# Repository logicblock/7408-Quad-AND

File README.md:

### Logic Block 7408 - Quad 2-input AND gates

*Scale 1:1*

### Where to buy it?
Coming soon on Tindie

### Licence
**Logic Block 7408 - Quad 2-input AND gates** are licenced under [Creative Commons Attribution and Share Alike 4.0 International](https://github.com/logicblock/7408-Quad-AND/blob/master/LICENSE.md) by [J.Rodrigo](http://www.jrodrigo.net).

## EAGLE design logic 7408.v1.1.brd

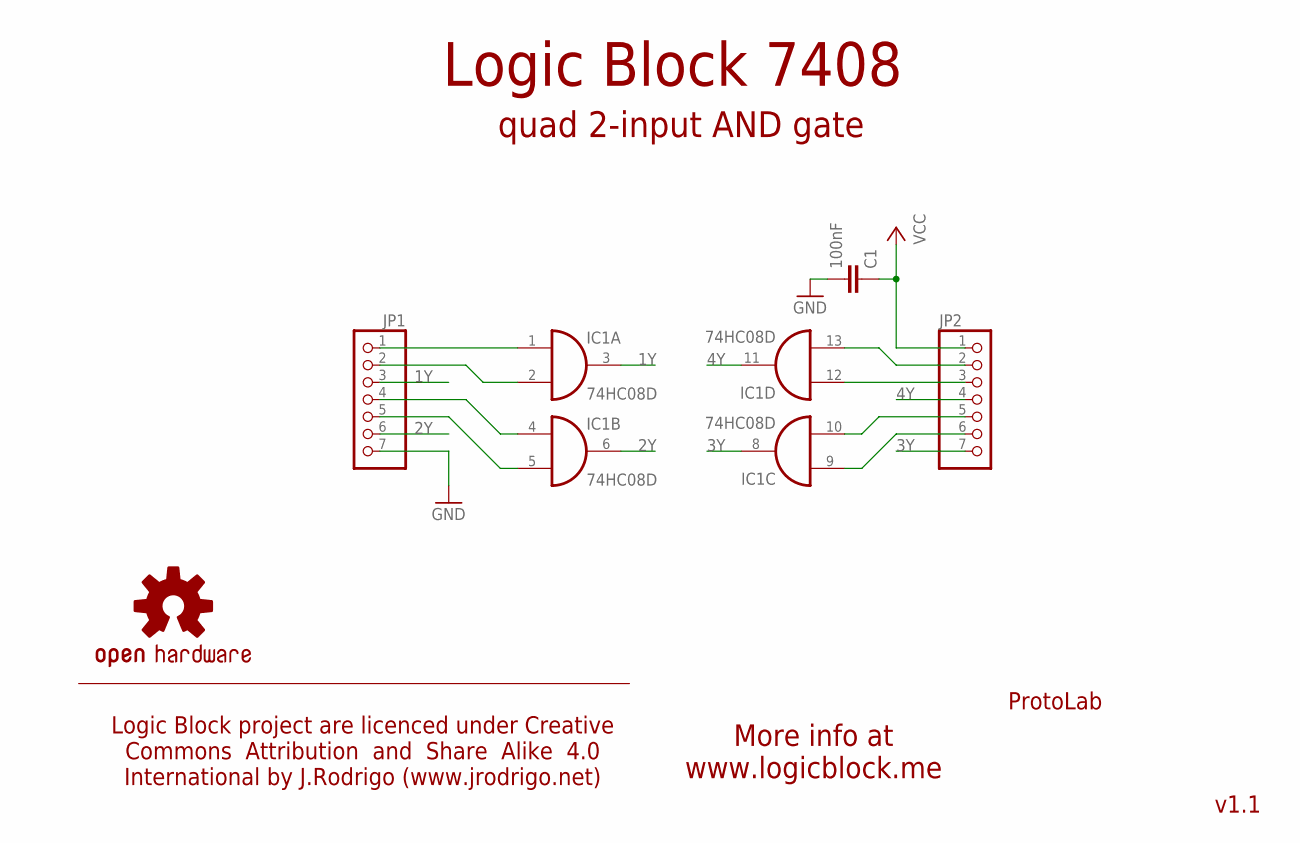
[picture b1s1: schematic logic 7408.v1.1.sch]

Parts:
C1: 100nF; C0805K
IC1: 74HC08D; SO14
JP1, JP2: CON_1X7CLEANBIG; CON_1X07-CLEANBIG
U$1: OSHW-LOGOS-LAYER230; OSHW-LOGO-S_LAYER230

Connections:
1Y: IC1.3 (O), JP1.3
2Y: IC1.6 (O), JP1.6
3Y: IC1.8 (O), JP2.7
4Y: IC1.11 (O), JP2.4
GND: C1.2, IC1.7 (GND), JP1.7
unnamed: IC1.1 (I0), JP1.1
unnamed: IC1.2 (I1), JP1.2
unnamed: IC1.9 (I0), JP2.6
unnamed: IC1.4 (I0), JP1.4
unnamed: IC1.5 (I1), JP1.5
unnamed: IC1.10 (I1), JP2.5
unnamed: IC1.12 (I0), JP2.3
unnamed: IC1.13 (I1), JP2.2
VCC: C1.1, IC1.14 (VCC), JP2.1

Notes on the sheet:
ProtoLab
v1.1
More info at www.logicblock.me
Logic Block 7408
quad 2-input AND gate
Logic Block project are licenced under Creative Commons Attribution and Share Alike 4.0 International by J.Rodrigo (www.jrodrigo.net)

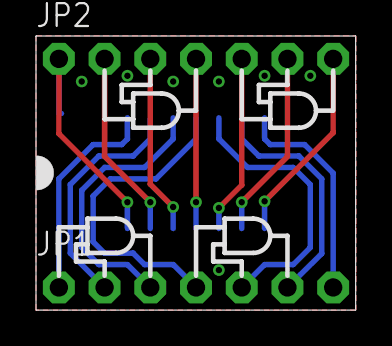
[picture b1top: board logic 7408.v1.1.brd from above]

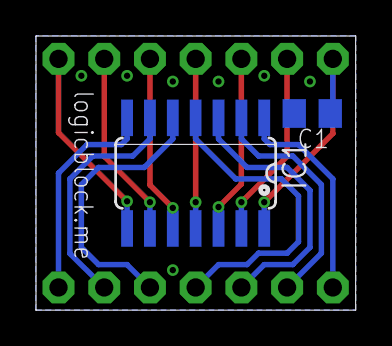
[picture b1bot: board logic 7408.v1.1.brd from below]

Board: 2 copper layers, 17.8 x 15.2 mm, 5 parts (2 on the bottom side), 14 nets.

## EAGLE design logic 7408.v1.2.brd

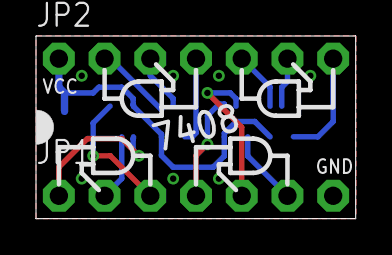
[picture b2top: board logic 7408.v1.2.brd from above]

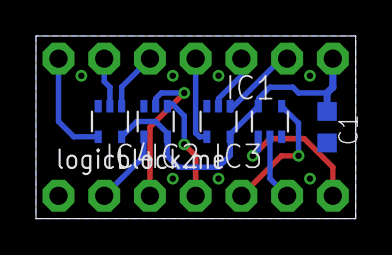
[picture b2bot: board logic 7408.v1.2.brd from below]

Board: 2 copper layers, 17.8 x 10.1 mm, 8 parts (5 on the bottom side), 14 nets.

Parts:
C1: 100nF; C0603K
IC1, IC2, IC3, IC4: SC70-5
JP1, JP2: CON_1X07-CLEANBIG
U$1: OSHW-LOGOS-LAYER230; OSHW-LOGO-S_LAYER230

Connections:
1Y: IC1.4, JP1.3
2Y: IC2.4, JP1.6
3Y: IC4.4, JP2.7
4Y: IC3.4, JP2.4
GND: C1.2, IC1.3, IC2.3, IC3.3, IC4.3, JP1.7
unnamed: IC1.1, JP1.1
unnamed: IC1.2, JP1.2
unnamed: IC4.2, JP2.6
unnamed: IC2.1, JP1.4
unnamed: IC2.2, JP1.5
unnamed: IC4.1, JP2.5
unnamed: IC3.2, JP2.3
unnamed: IC3.1, JP2.2
VCC: C1.1, IC1.5, IC2.5, IC3.5, IC4.5, JP2.1

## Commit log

2015-10-29 Created
2015-10-29 Created README.md
2015-11-26 Fixed silkscreen
2015-11-26 Fixed
    Fixed small text error
2015-11-26 Revert "Fixed silkscreen"
    This reverts commit 4234e274ace9d68fc27a52361f0495f19ad678bf.
